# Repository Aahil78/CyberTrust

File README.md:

# CyberTrust
CyberTrust Is A RP2350A Based Security Key, it can be used as a FIDO2 Secure Key for secure authentication and account safety.

Features:
- Custom PCB
- Custom Enclosure
- Based on the RP2350A MCU
- WS2812B RGB LED
- User Presence Button
- USB-A Male Port
- OSH and OSS

## Images
### PCB

### Schematic

### Enclosure/Assembly

## Bill Of Materials

| Comment           | Designator                           | Footprint                                           | LCSC Part # | Quantity | Total Price |
|-------------------|--------------------------------------|-----------------------------------------------------|-------------|----------|-------------|
| RP2350_60QFN      | U1                                   | RP2350-QFN-60-1EP_7x7_P0.4mm_EP3.4x3.4mm_ThermalVias| C42411118   | 1        | $ 1.65      |
| 4.7u              | C10, C6, C7, C9                      | 0402                                                | C23733      | 4        | $ 0.26      |
| 15p               | C3, C4                               | 0402                                                | C1548       | 2        | $ 0.1       |
| 33                | R5                                   | 0402                                                | C25105      | 1        | $ 0.06      |
| USB3_A            | J1                                   | USB3_A_Plug_Wuerth_692112030100_Horizontal          | C7527682    | 1        | $ 0.44      |
| WS2812B           | D1                                   | LED_WS2812B_PLCC4_5.0x5.0mm_P3.2mm                  | C2761795    | 1        | $ 0.41      |
| 1k                | R2, R4, R6                           | 0402                                                | C11702      | 3        | $ 0.06      |
| NCP1117-3.3_SOT223| U2                                   | SOT-223-3_TabPin2                                   | C26537      | 1        | $ 1.31      |
| 3.3u              | L1                                   | L_pol_2016                                          | C42411119   | 1        | $ 1.29      |
| 0                 | R10                                  | 0402                                                | C17168      | 1        | $ 0.06      |
| W25Q128JVS        | U3                                   | SOIC-8_5.23x5.23mm_P1.27mm                          | C97521      | 1        | $ 0.76      |
| SW_Push           | SW3                                  | SW_Push_SPST_NO_Alps_SKRK                           | C115357     | 1        | $ 0.63      |
| 330Ω              | R3                                   | 0805                                                | C17630      | 1        | $ 0.19      |
| 10u               | C1, C19, C5                          | 0805                                                | C15850      | 3        | $ 0.22      |
| 100n              | C11, C12, C13, C14, C15, C16, C17, C18, C2, C8 | 0402                                      | C1525       | 10       | $ 0.12      |
| SW_Push           | SW1, SW2                             | SW_Push_1P1T_NO_Vertical_Wuerth_434133025816        | C5504987    | 2        | $ 1.86      |
| ABM8-272-T3       | Y1                                   | Crystal_SMD_3225-4Pin_3.2x2.5mm                     | C20625731   | 1        | $ 0.37      |
| 27                | R7, R8                               | 0402                                                | C25100      | 2        | $ 0.06      |

## Additional Stuff
- PCB - $4.2
- Enclosure (3D Printed Case and Top) - Bottom: $10.89, Top(Transparent Resin): $14.40
- Screws - $0.132
- PCBA Costs - $60.66 (I need to solder RGBs, MOQ: 5, Total Cost: $0.41)

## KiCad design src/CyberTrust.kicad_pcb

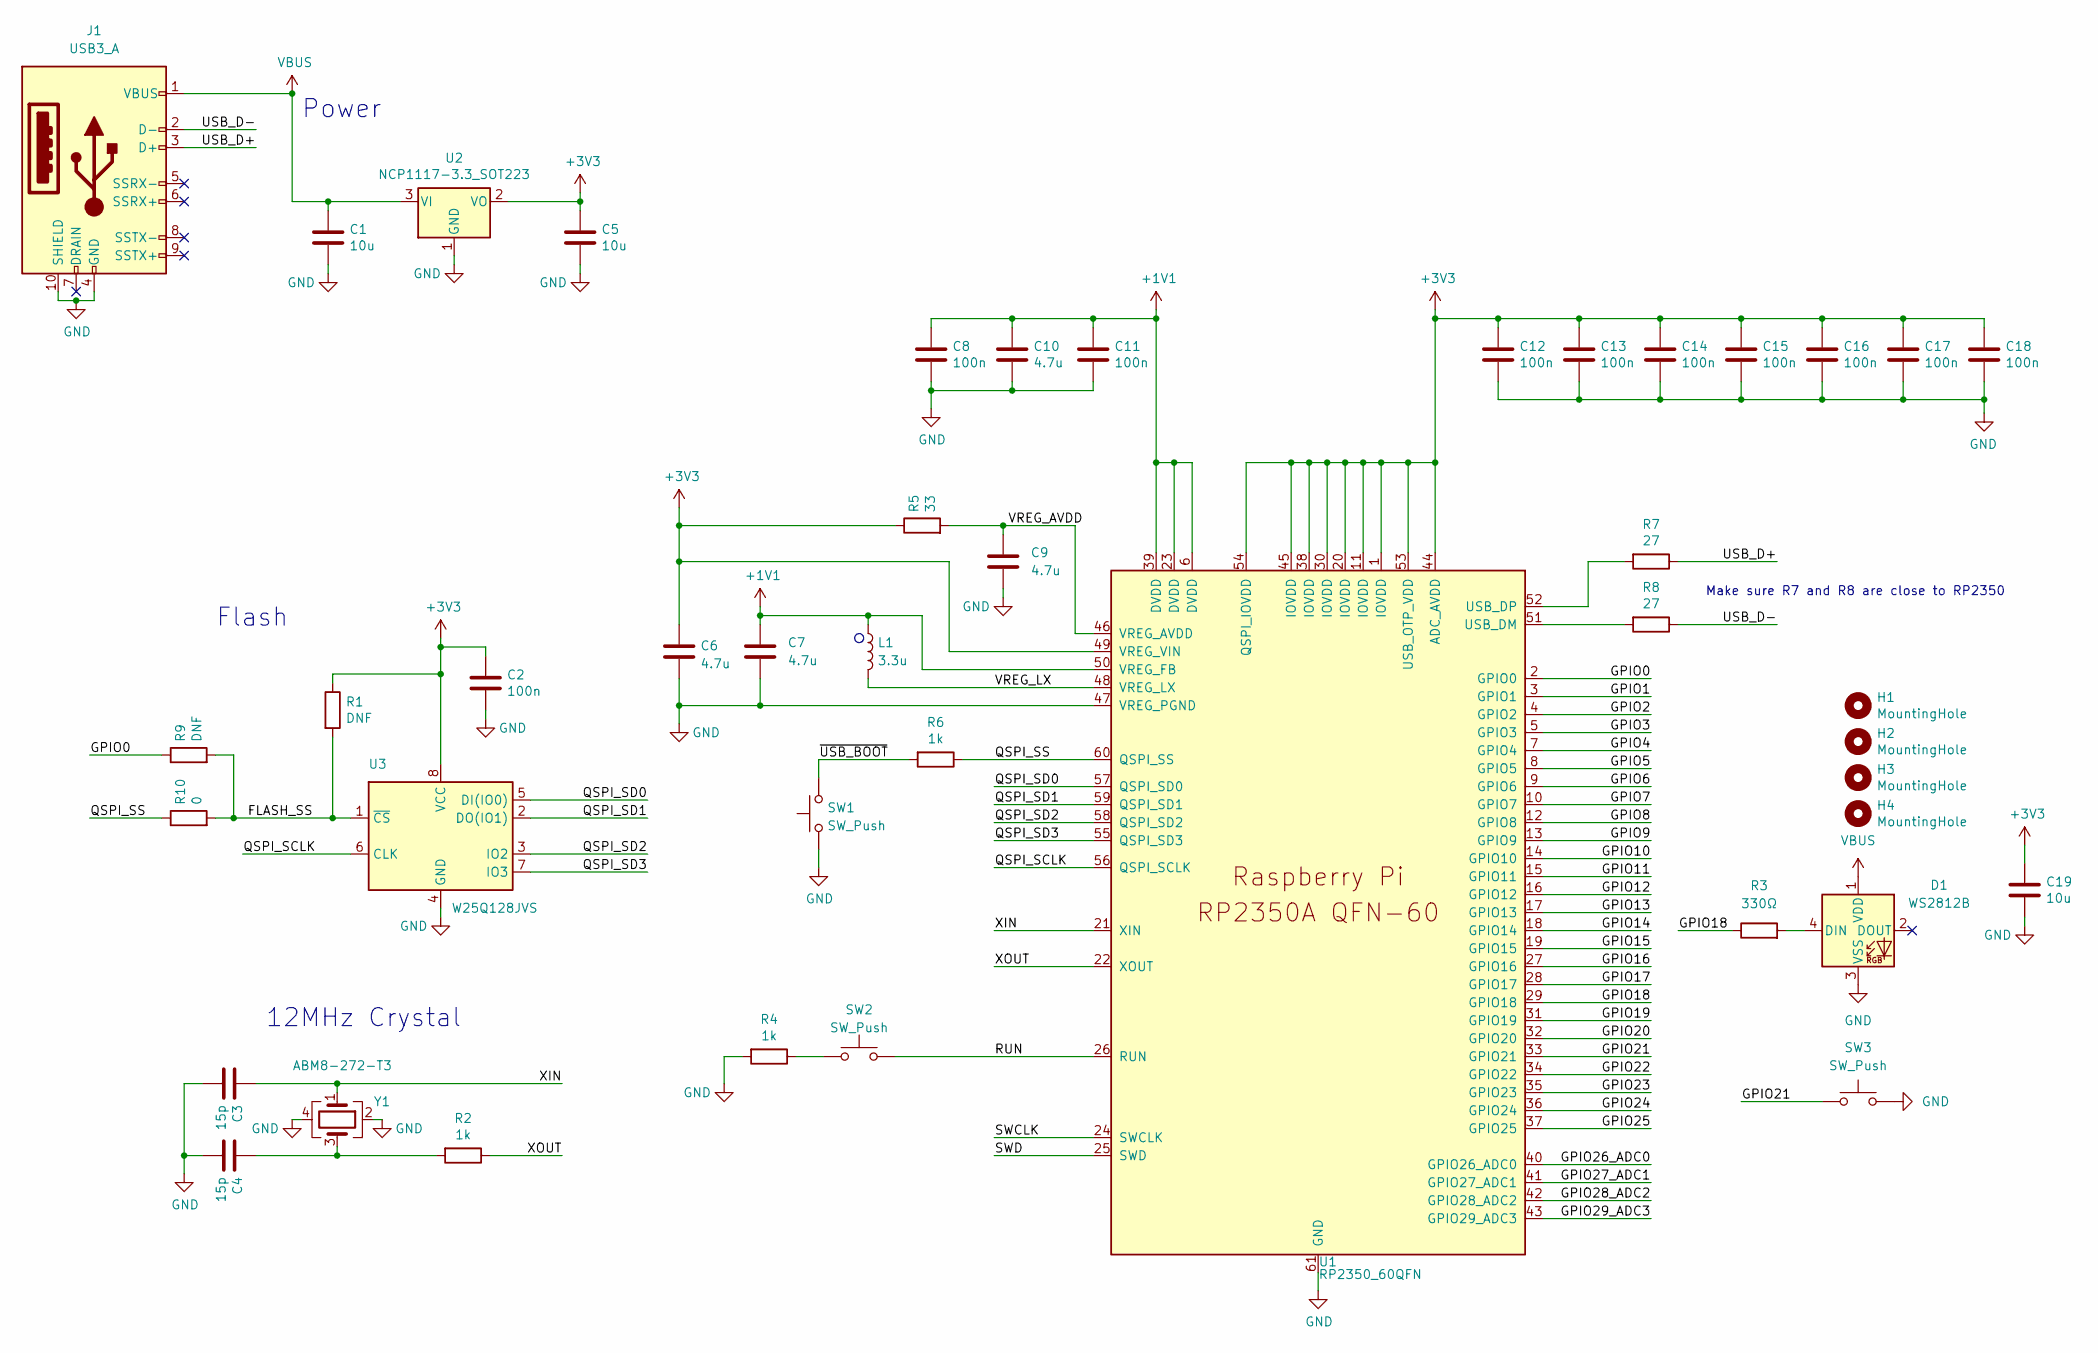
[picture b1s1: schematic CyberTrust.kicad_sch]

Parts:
C1, C5, C19: 10u; C_0805_2012Metric
C2, C8, C11, C12, C13, C14, C15, C16, C17, C18: 100n; C_0402_1005Metric
C3, C4: 15p; C_0402_1005Metric
C6, C7: 4.7u; C_0402_1005Metric_small_pads
C9, C10: 4.7u; C_0402_1005Metric
D1: WS2812B; LED_WS2812B_PLCC4_5.0x5.0mm_P3.2mm
H1, H2, H3, H4: MountingHole; MountingHole_2.7mm_M2.5
J1: USB3_A; USB3_A_Plug_Wuerth_692112030100_Horizontal
L1: 3.3u; L_pol_2016
R1, R9: DNF; R_0402_1005Metric
R2, R4, R6: 1k; R_0402_1005Metric
R3: 330Ω; R_0805_2012Metric_Pad1.20x1.40mm_HandSolder
R5: 33; R_0402_1005Metric
R7, R8: 27; R_0402_1005Metric
R10: 0; R_0402_1005Metric
SW1, SW2: SW_Push; SW_Push_1P1T_NO_Vertical_Wuerth_434133025816
SW3: SW_Push; SW_Push_SPST_NO_Alps_SKRK
U1: RP2350_60QFN; RP2350-QFN-60-1EP_7x7_P0.4mm_EP3.4x3.4mm_ThermalVias
U2: NCP1117-3.3_SOT223; SOT-223-3_TabPin2
U3: W25Q128JVS; SOIC-8_5.23x5.23mm_P1.27mm
Y1: ABM8-272-T3; Crystal_SMD_3225-4Pin_3.2x2.5mm

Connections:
+1V1: C7.1, C8.1, C10.1, C11.1, L1.1, U1.6 (DVDD), U1.23 (DVDD), U1.39 (DVDD), U1.50 (VREG_FB)
+3V3: C2.1, C5.1, C6.1, C12.1, C13.1, C14.1, C15.1, C16.1, C17.1, C18.1, C19.1, R1.1, R5.1, U1.1 (IOVDD), U1.11 (IOVDD), U1.20 (IOVDD), U1.30 (IOVDD), U1.38 (IOVDD), U1.44 (ADC_AVDD), U1.45 (IOVDD), U1.49 (VREG_VIN), U1.53 (USB_OTP_VDD), U1.54 (QSPI_IOVDD), U2.2 (VO), U3.8 (VCC)
/FLASH_SS: R1.2, R9.2, R10.2, U3.1 (~CS)
/GPIO0: R9.1, U1.2 (GPIO0)
/GPIO1: U1.3 (GPIO1)
/GPIO2: U1.4 (GPIO2)
/GPIO3: U1.5 (GPIO3)
/GPIO4: U1.7 (GPIO4)
/GPIO5: U1.8 (GPIO5)
/GPIO6: U1.9 (GPIO6)
/GPIO7: U1.10 (GPIO7)
/GPIO8: U1.12 (GPIO8)
/GPIO9: U1.13 (GPIO9)
/GPIO10: U1.14 (GPIO10)
/GPIO11: U1.15 (GPIO11)
/GPIO12: U1.16 (GPIO12)
/GPIO13: U1.17 (GPIO13)
/GPIO14: U1.18 (GPIO14)
/GPIO15: U1.19 (GPIO15)
/GPIO16: U1.27 (GPIO16)
/GPIO17: U1.28 (GPIO17)
/GPIO18: R3.1, U1.29 (GPIO18)
/GPIO19: U1.31 (GPIO19)
/GPIO20: U1.32 (GPIO20)
/GPIO21: SW3.1, U1.33 (GPIO21)
/GPIO22: U1.34 (GPIO22)
/GPIO23: U1.35 (GPIO23)
/GPIO24: U1.36 (GPIO24)
/GPIO25: U1.37 (GPIO25)
/GPIO26_ADC0: U1.40 (GPIO26_ADC0)
/GPIO27_ADC1: U1.41 (GPIO27_ADC1)
/GPIO28_ADC2: U1.42 (GPIO28_ADC2)
/GPIO29_ADC3: U1.43 (GPIO29_ADC3)
/QSPI_SCLK: U1.56 (QSPI_SCLK), U3.6 (CLK)
/QSPI_SD0: U1.57 (QSPI_SD0), U3.5 (DI(IO0))
/QSPI_SD1: U1.59 (QSPI_SD1), U3.2 (DO(IO1))
/QSPI_SD2: U1.58 (QSPI_SD2), U3.3 (IO2)
/QSPI_SD3: U1.55 (QSPI_SD3), U3.7 (IO3)
/QSPI_SS: R6.1, R10.1, U1.60 (QSPI_SS)
/RUN: SW2.2, U1.26 (RUN)
/SWCLK: U1.24 (SWCLK)
/SWD: U1.25 (SWD)
/USB_D+: J1.3 (D+), R7.1
/USB_D-: J1.2 (D-), R8.1
/VREG_AVDD: C9.1, R5.2, U1.46 (VREG_AVDD)
/VREG_LX: L1.2, U1.48 (VREG_LX)
/XIN: C3.1, U1.21 (XIN), Y1.1
/XOUT: R2.1, U1.22 (XOUT)
/~USB_BOOT: R6.2, SW1.2
GND: C1.2, C2.2, C3.2, C4.2, C5.2, C6.2, C7.2, C8.2, C9.2, C10.2, C11.2, C12.2, C13.2, C14.2, C15.2, C16.2, C17.2, C18.2, C19.2, D1.3 (VSS), J1.4 (GND), J1.10 (SHIELD), R4.2, SW1.1, SW3.2, U1.47 (VREG_PGND), U1.61 (GND), U2.1 (GND), U3.4 (GND), Y1.2, Y1.4
unnamed: C4.1, R2.2, Y1.3
unnamed: D1.4 (DIN), R3.2
unnamed: R4.1, SW2.1
unnamed: R8.2, U1.51 (USB_DM)
unnamed: R7.2, U1.52 (USB_DP)
VBUS: C1.1, D1.1 (VDD), J1.1 (VBUS), U2.3 (VI)

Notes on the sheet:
Flash
Make sure R7 and R8 are close to RP2350
12MHz Crystal
Power

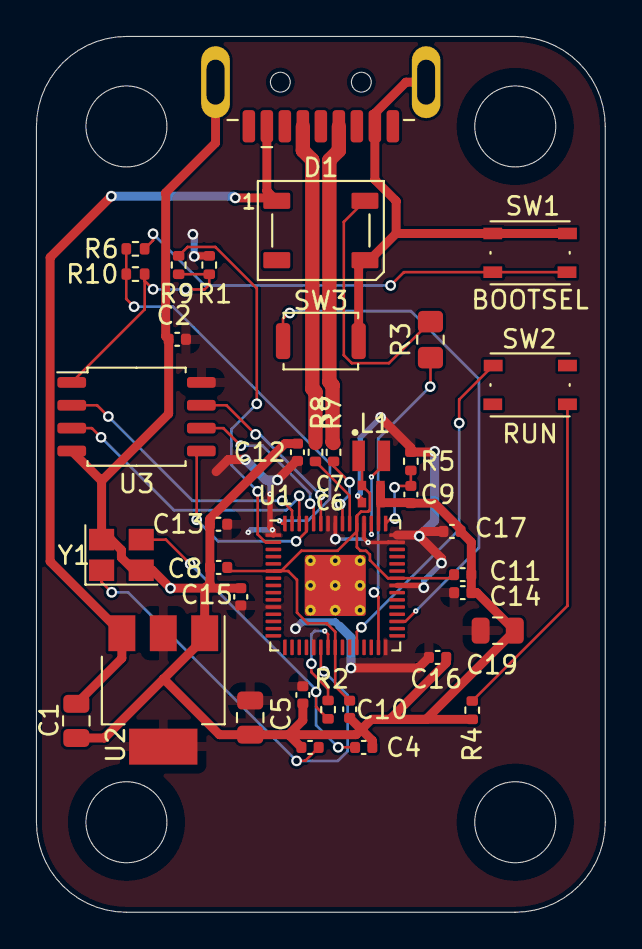
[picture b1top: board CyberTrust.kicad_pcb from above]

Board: 2 copper layers, 31.6 x 48.7 mm, 43 parts (0 on the bottom side), 27 nets.

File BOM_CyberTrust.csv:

Comment,Designator,Footprint,LCSC Part #,Quantity,Total Price
RP2350_60QFN,U1,RP2350-QFN-60-1EP_7x7_P0.4mm_EP3.4x3.4mm_ThermalVias,C42411118,1,$1.65
4.7u,"C10, C6, C7, C9",402,C23733,4,$0.26
15p,"C3, C4",402,C1548,2,$0.10
33,R5,402,C25105,1,$0.06
USB3_A,J1,USB3_A_Plug_Wuerth_692112030100_Horizontal,C7527682,1,$0.44
WS2812B,D1,LED_WS2812B_PLCC4_5.0x5.0mm_P3.2mm,C2761795,1,$0.41
1k,"R2, R4, R6",402,C11702,3,$0.06
NCP1117-3.3_SOT223,U2,SOT-223-3_TabPin2,C26537,1,$1.31
3.3u,L1,L_pol_2016,C42411119,1,$1.29
0,R10,402,C17168,1,$0.06
W25Q128JVS,U3,SOIC-8_5.23x5.23mm_P1.27mm,C97521,1,$0.76
SW_Push,SW3,SW_Push_SPST_NO_Alps_SKRK,C115357,1,$0.63
330Ω,R3,805,C17630,1,$0.19
10u,"C1, C19, C5",805,C15850,3,$0.22
100n,"C11, C12, C13, C14, C15, C16, C17, C18, C2, C8",402,C1525,10,$0.12
SW_Push,"SW1, SW2",SW_Push_1P1T_NO_Vertical_Wuerth_434133025816,C5504987,2,$1.86
ABM8-272-T3,Y1,Crystal_SMD_3225-4Pin_3.2x2.5mm,C20625731,1,$0.37
27,"R7, R8",402,C25100,2,$0.06
,,,,,
Additonal Stuff:,,,,,
PCB,,,,,
Enclosure (3D Printed Case and acrylic top),,,,,
Screws,,,,,
"PCBA Costs - I'll need PCBA unless if I can buy a hotplate with my stuff as I don't own one, ying a hotplate would be cheaper)",,,,,
SMT Stencil/Solder Paste (if using hotplate),,,,,

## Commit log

2025-06-29 Add all files
2025-07-06 Fix a typo
